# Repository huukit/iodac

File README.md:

# iodac
The Proximia iodac is an isolated Digital-in to 0-10V out controller for applications that require conversion from a digital signal to a analog voltage output.

Such application are for example AC-blowers that usually need a 0-10V input but the HMI is a button interface.

Features:
* 5V input voltage.
* Fully isolated power supply.
* 5 fully isolated low-active inputs. (5V)
* Each input can be configured to a specific output voltage.
* 1 0-10V output. (25mA max load)

The operating mode currently follows the input active with the highest number input having the highest priority, but
the source can be modified for operation where the output will hold the last value. (Pulsed input signal).

# Schematic

## Pins
### JP1
Inputs 1-5, VCC (+5V, GND) .
### JP2
Debug header for isolated inputs.
### JP3
0-10V output adjust pins.
### JP4
0-10V output.

# Connection example

## Connecting
1. Locate the GND and +5V supply lines in the controlling device.
1. Connect the GND line to JP1.7 and +5V to JP1.6.
1. Locate the outputs (buttons or leds) on the controlling device, and make sure they are low-active.
1. Connect the lowest priority output (i.e. 1) to JP1.1 and then the rest of the outputs as required in order. 
Remember, that the highest number input will have priority. That is, if input 3 is active, input 1 will be ignored.
 
## Adjusting output voltage
1. Connect a multimeter to the output (JP4.1 + JP4.2). Remember to use the correct GND for measurements!
1. Activete the input that is to be adjusted.
1. Optionally connect a button between JP3.1 <-> JP4.2 and JP3.2 <-> JP4.2. A simple wire to toggle the pins can also be used.
1. Measure the output while adjusting the voltage with the buttons (or use the wire).
1. Repeat for each active input.

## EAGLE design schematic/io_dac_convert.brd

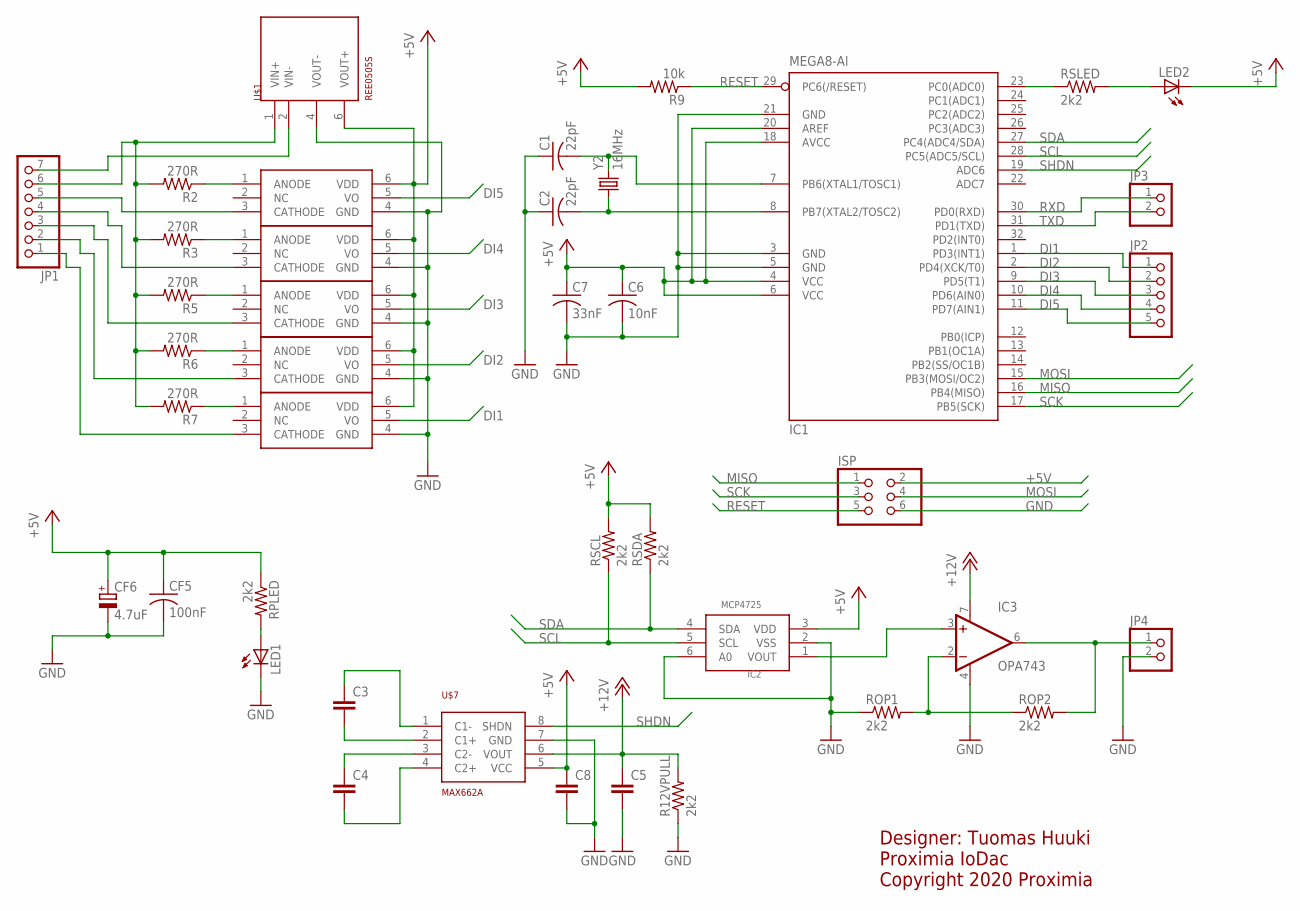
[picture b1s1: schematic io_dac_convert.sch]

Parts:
C1, C2: 22pF; C0603
C3, C4, C5, C8: C-EUC1206; C1206
C6: 10nF; C0603
C7: 33nF; C0603
CF5: 100nF; C0603
CF6: 4.7uF; PANASONIC_B
IC1: MEGA8-AI; TQFP32-08
IC2: MCP4725; SOT23-6
IC3: OPA743; SO08
ISP: PINHD-2X3; 2X03
JP1: PINHD-1X7; 1X07
JP2: PINHD-1X5; 1X05
JP3, JP4: PINHD-1X2; 1X02
LED1, LED2: LEDSML1206; SML1206
R2, R3, R5, R6, R7: 270R; R0603
R9: 10k; R0603
R12VPULL: 2k2; R0603
ROP1, ROP2: 2k2; R0603
RPLED: 2k2; R0603
RSCL: 2k2; R0603
RSDA: 2k2; R0603
RSLED: 2k2; R0603
U$1: REE0505S; SIP-6
U$2, U$3, U$4, U$5, U$6: SI8710; SDIP-6
U$7: MAX662A; SO8
Y2: 16MHz; CRYSTAL-SMD-5X3

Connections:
+5V: C6.1, C7.1, C8.1, CF5.1, CF6.+, IC1.4 (VCC), IC1.6 (VCC), IC1.18 (AVCC), IC1.20 (AREF), IC2.3 (VDD), ISP.2, LED2.C, R9.2, RPLED.1, RSCL.2, RSDA.2, U$1.6 (VOUT+), U$2.6 (VDD), U$3.6 (VDD), U$4.6 (VDD), U$5.6 (VDD), U$6.6 (VDD), U$7.5 (VCC)
+12V: C5.1, IC3.7 (V+), R12VPULL.2, U$7.6 (VOUT)
DI1: IC1.1 (PD3(INT1)), JP2.1, U$6.5 (VO)
DI2: IC1.2 (PD4(XCK/T0)), JP2.2, U$5.5 (VO)
DI3: IC1.9 (PD5(T1)), JP2.3, U$4.5 (VO)
DI4: IC1.10 (PD6(AIN0)), JP2.4, U$3.5 (VO)
DI5: IC1.11 (PD7(AIN1)), JP2.5, U$2.5 (VO)
GND: C1.1, C2.1, C5.2, C6.2, C7.2, C8.2, CF5.2, CF6.-, IC1.3 (GND), IC1.5 (GND), IC1.21 (GND), IC2.2 (VSS), IC2.6 (A0), IC3.4 (V-), ISP.6, JP4.2, LED1.C, R12VPULL.1, ROP1.1, U$1.4 (VOUT-), U$2.4 (GND), U$3.4 (GND), U$4.4 (GND), U$5.4 (GND), U$6.4 (GND), U$7.7 (GND)
GND_EXT: JP1.7, U$1.2 (VIN-)
MISO: IC1.16 (PB4(MISO)), ISP.1
MOSI: IC1.15 (PB3(MOSI/OC2)), ISP.4
unnamed: LED1.A, RPLED.2
unnamed: IC1.23 (PC0(ADC0)), RSLED.1
unnamed: JP1.6, R2.2, R3.2, R5.2, R6.2, R7.2, U$1.1 (VIN+)
unnamed: R2.1, U$2.1 (ANODE)
unnamed: JP1.5, U$2.3 (CATHODE)
unnamed: R3.1, U$3.1 (ANODE)
unnamed: R5.1, U$4.1 (ANODE)
unnamed: R6.1, U$5.1 (ANODE)
unnamed: R7.1, U$6.1 (ANODE)
unnamed: JP1.4, U$3.3 (CATHODE)
unnamed: JP1.3, U$4.3 (CATHODE)
unnamed: JP1.2, U$5.3 (CATHODE)
unnamed: JP1.1, U$6.3 (CATHODE)
unnamed: C2.2, IC1.8 (PB7(XTAL2/TOSC2)), Y2.1
unnamed: C1.2, IC1.7 (PB6(XTAL1/TOSC1)), Y2.3 (2)
unnamed: C3.2, U$7.2 (C1+)
unnamed: IC2.1 (VOUT), IC3.3 (+IN)
unnamed: IC3.6 (OUT), JP4.1, ROP2.2
unnamed: IC3.2 (-IN), ROP1.2, ROP2.1
unnamed: C3.1, U$7.1 (C1-)
unnamed: LED2.A, RSLED.2
unnamed: C4.1, U$7.3 (C2-)
unnamed: C4.2, U$7.4 (C2+)
RESET: IC1.29 (PC6(/RESET)), ISP.5, R9.1
RXD: IC1.30 (PD0(RXD)), JP3.1
SCK: IC1.17 (PB5(SCK)), ISP.3
SCL: IC1.28 (PC5(ADC5/SCL)), IC2.5 (SCL), RSCL.1
SDA: IC1.27 (PC4(ADC4/SDA)), IC2.4 (SDA), RSDA.1
SHDN: IC1.19 (ADC6), U$7.8 (SHDN)
TXD: IC1.31 (PD1(TXD)), JP3.2

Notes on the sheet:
Designer: Tuomas Huuki Proximia IoDac Copyright 2020 Proximia

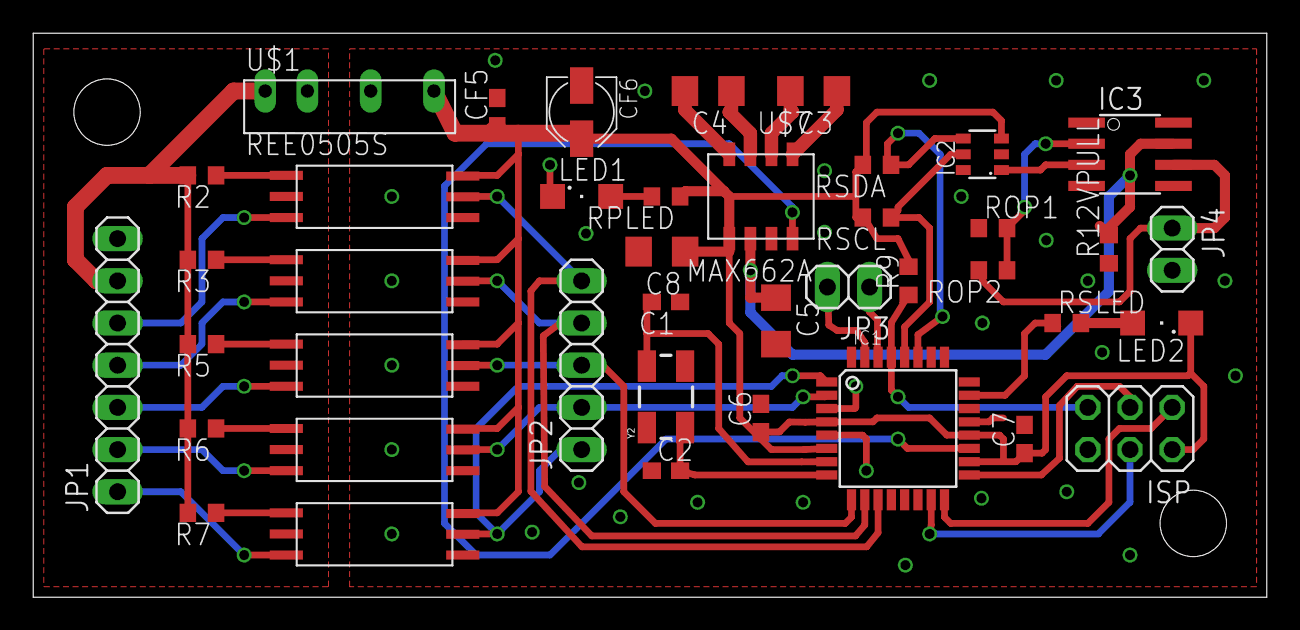
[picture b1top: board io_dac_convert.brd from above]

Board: 2 copper layers, 74.3 x 34.0 mm, 41 parts (0 on the bottom side), 41 nets.

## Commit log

2020-06-22 Initial schematics for I/O converter
2020-06-26 Moved schematics to correct dir.
2020-07-31 Adding source code for board.
2020-08-04 Adding functionality to configure each output voltage separately.
2020-08-24 Added instructional picture and picture of schematic.
2020-08-24 Updated readme with instructions on connecting the device.

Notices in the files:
schematic/io_dac_convert.brd:
(c) 2020 Tuomas Huuki
parts and their libraries:
SparkFun-FreqCtrl: Licensing: CC v3.0 Share-Alike You are welcome to use this library for commercial purposes.
